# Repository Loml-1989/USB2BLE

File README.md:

# USB2BLE
USB2BLE is a project designed to convert a USB controller into a Bluetooth gamepad.
It uses a Seeed Studio XIAO ESP32 S3 acting as a USB Host to read the USB.
## Features
- **USB Host to Bluetooth Translation:** Intercepts raw USB HID data from a controller and broadcasts it as a standard Bluetooth gamepad to PCs and mobile devices.
- **Integrated Power:** MT3608 steps up the 3.7V LiPo battery to the 5V (required by the USB).
## Gallery

## Enclosure
Assembly hardware requires M2 x 8mm Socket Head Cap screws. The space under the PBC is meant to for the flat LiPo battery pack.
Link: https://cad.onshape.com/documents/79600c89bc90443b04a0eccc/w/c9c8aab0a155c9fbc029d97b/e/64e19027fa4e67c0d8740c29
## Firmware Setup
Because the ESP32 S3 must act as a USB host, this project relies on the native ESP32 TinyUSB stack. Currently the firmware DOES NOT work to translate the controller's inputs. The current firmware prints the output data when a button is pressed the reason is that every controller has different mappings so first we need to find that mapping then map it in the firmware only then it will work.
### Required Library:
- [ESP32-BLE-Gamepad](https://github.com/lemmingDev/ESP32-BLE-Gamepad "null") (by lemmingDev)

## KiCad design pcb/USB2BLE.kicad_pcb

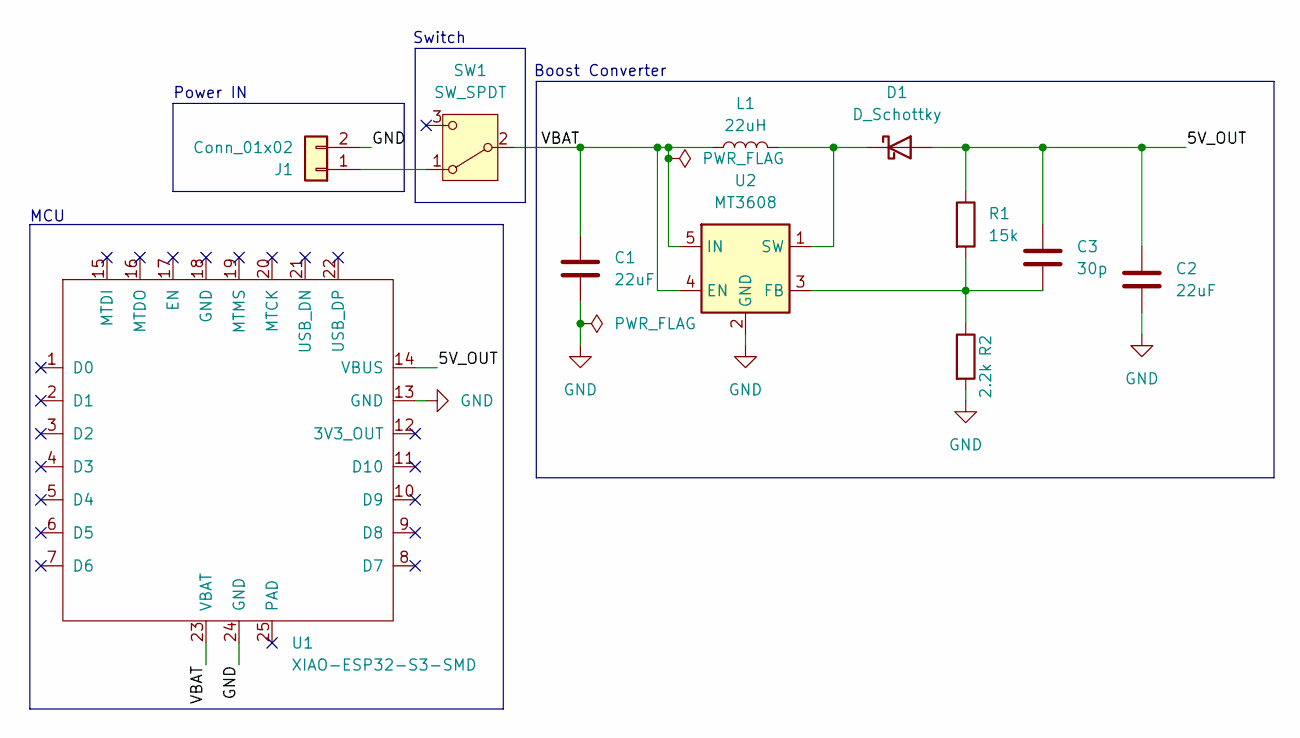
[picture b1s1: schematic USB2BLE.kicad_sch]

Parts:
C1, C2: 22uF; C_0805_2012Metric_Pad1.18x1.45mm_HandSolder
C3: 30p; C_0805_2012Metric_Pad1.18x1.45mm_HandSolder
D1: D_Schottky; D_SMA
J1: Conn_01x02; JST_PH_S2B-PH-K_1x02_P2.00mm_Horizontal
L1: 22uH; L_Taiyo-Yuden_NR-20xx
R1: 15k; R_0805_2012Metric_Pad1.20x1.40mm_HandSolder
R2: 2.2k; R_0805_2012Metric_Pad1.20x1.40mm_HandSolder
SW1: SW_SPDT; SW_Slide_SPDT_Straight_CK_OS102011MS2Q
U1: XIAO-ESP32-S3-SMD
U2: MT3608; SOT-23-6

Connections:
/5V_OUT: C2.1, C3.1, D1.2 (A), R1.1, U1.14 (VBUS)
/VBAT: C1.1, L1.1, SW1.2 (B), U1.23 (VBAT), U2.4 (EN), U2.5 (IN)
GND: C1.2, C2.2, J1.2, R2.2, U1.13 (GND), U1.24 (GND), U2.2 (GND)
unnamed: D1.1 (K), L1.2, U2.1 (SW)
unnamed: J1.1, SW1.1 (A)
unnamed: C3.2, R1.2, R2.1, U2.3 (FB)

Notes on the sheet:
Switch
Boost Converter
MCU
Power IN

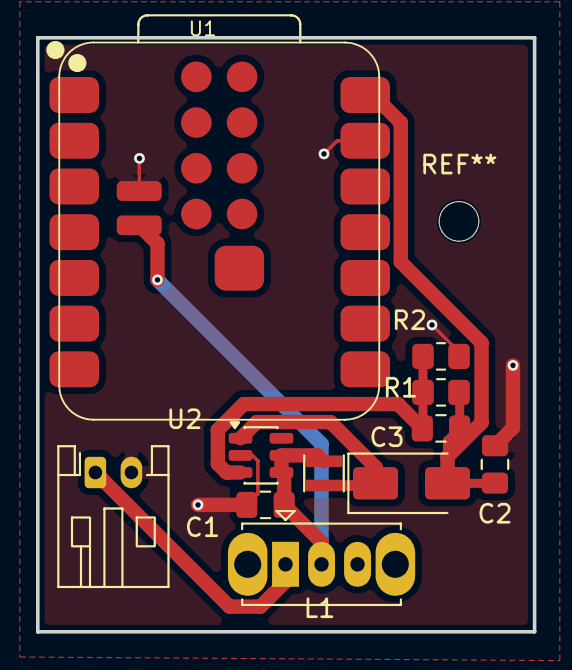
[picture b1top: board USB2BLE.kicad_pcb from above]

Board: 2 copper layers, 27.6 x 33.0 mm, 11 parts (0 on the bottom side), 6 nets.

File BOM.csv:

Id,Designator,Footprint,Quantity,Designation,Item link,Price INR,Price USD
1,"C1, C2",C_0805_2012Metric_Pad1.18x1.45mm_HandSolder,2,C,https://www.ktron.in/product/22uf-25v-multi-layered-ceramic-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,32,$1
2,D1,D_SMA,1,D_Schottky,https://robu.in/product/ss34-slkor-40v-500mv3a-3a-smado-214a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,4,$1
3,J1,JST_PH_S2B-PH-K_1x02_P2.00mm_Horizontal,1,Conn_01x02,https://robocraze.com/products/2-mm-pitch-jst-cable-with-con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,1,$1
4,L1,L_1210_3225Metric,1,L,https://robu.in/product/swpa4030s220mt-sunlord-22uh-1a-20-29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,92,$1
5,R1,R_0805_2012Metric_Pad1.20x1.40mm_HandSolder,1,15k,https://www.ktron.in/product/resistor-15k-ohms-1-1-16w-smd-0402/,13,$1
6,R2,R_0805_2012Metric_Pad1.20x1.40mm_HandSolder,1,2.2k,https://robu.in/product/yageo-2-2k-ohm-1-4w-0805-surface-mou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,1,$1
7,SW1,SW_Slide_SPDT_Straight_CK_OS102011MS2Q,1,SW_SPDT,https://robu.in/product/4mm-spdt-1p2t-slide-switch-pack-of-10/,3,$1
8,U1,XIAO-ESP32-S3-SMD,1,XIAO-ESP32-S3-SMD,https://robu.in/product/seeed-studio-xiao-esp32s3-2-4ghz-wif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,1139,$12
9,U2,SOT-23-6,1,MT3608,https://robu.in/product/mt3608-xian-aerosemi-tech-boost-type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,18,$1
10,,Battery,1,,https://robu.in/product/1250mah-pcm-protected-micro-li-po-battery/,459,$5
11,,Screws,1,,https://robu.in/product/easymech-set-m2-x-8mm-socket-head-ca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,219,$3
12,,PCB,5,,https://robu.in/product/online-pcb-manufacturing-service/,1000,$11
,,,,,,2981,$39
